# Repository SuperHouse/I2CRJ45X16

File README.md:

I2C to RJ45 Breakout (16 Port)
==============================
Copyright 2019-2021 SuperHouse Automation Pty Ltd  www.superhouse.tv  

24 RJ45 sockets connected to 64 I/O channels via I2C addressable
I/O controllers. Intended for use in building a home automation light
switch controller for connection to SuperHouse light switches.

Features:

 * 16 x RJ45 sockets for connection to light switches over Cat-5
 * I2C interface with interrupt output

This project has different versions:

 * 8-port version: https://github.com/superhouse/i2crj45x8
 * 16-port version: https://github.com/superhouse/i2crj45x16
 * 24-port version: https://github.com/superhouse/i2crj45x24
 * 24-port version with passthrough: https://github.com/superhouse/i2crj45x24pt

More information:

  http://www.superhouse.tv/i2crj45x16

INSTALLATION
------------
The design is saved as an EAGLE project. EAGLE PCB design software is
available from www.cadsoftusa.com free for non-commercial use. To use
this project download it and place the directory containing these files
into the "eagle" directory on your computer. Then open EAGLE and
navigate to the project.

CREDITS
-------
Designed by Jonathan Oxer jon@oxer.com.au

DISTRIBUTION
------------
The specific terms of distribution of this project are governed by the
license referenced below.

LICENSE
-------
Licensed under the TAPR Open Hardware License (www.tapr.org/OHL).
The "license" folder within this repository also contains a copy of
this license in plain text format.

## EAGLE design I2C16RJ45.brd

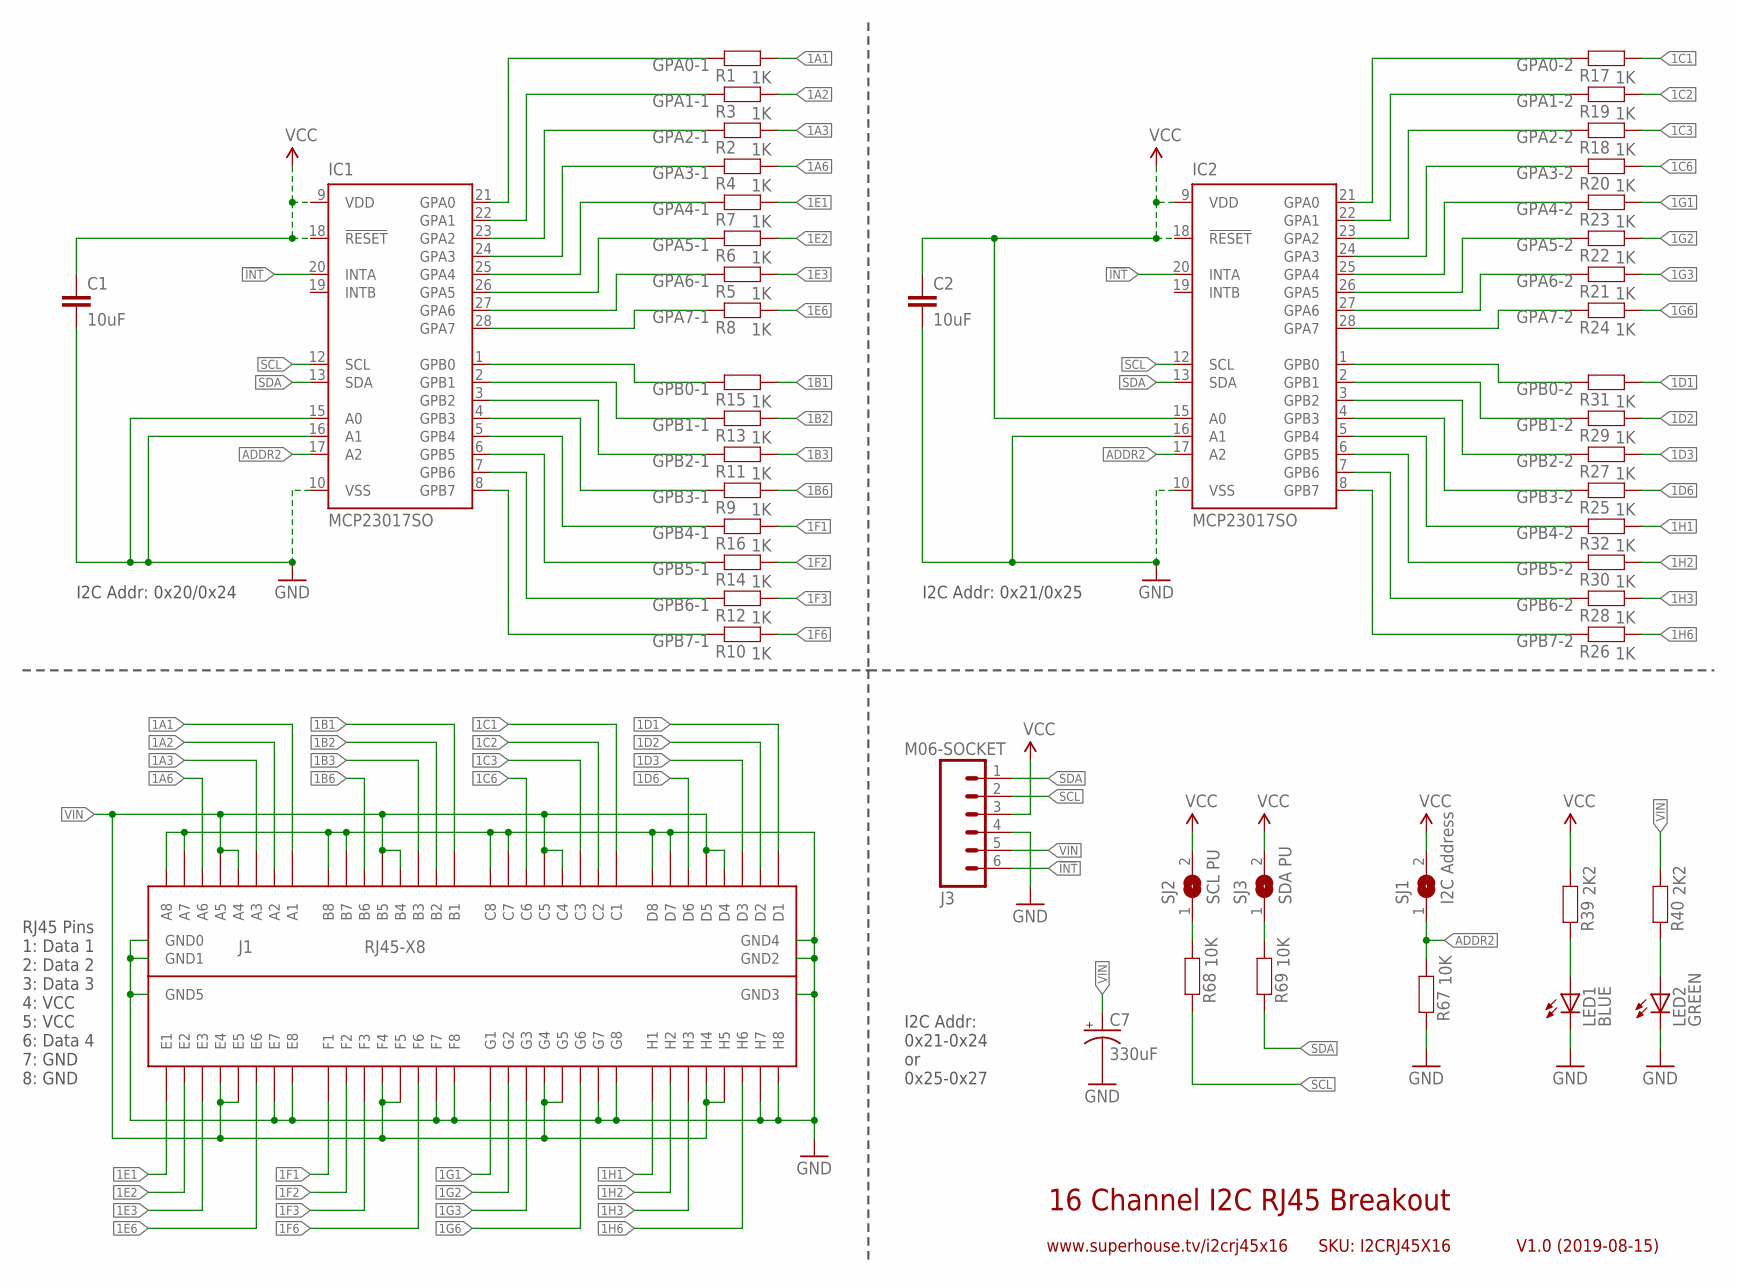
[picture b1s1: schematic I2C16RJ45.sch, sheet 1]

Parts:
C1, C2: 10uF; C0805
C7: 330uF; PANASONIC_G
IC1, IC2: MCP23017SO; SO28W
J1: RJ45-X8; RJ45-2X4
J3: M06-SOCKET; 1X06-S
LED1: BLUE; LED-0603
LED2: GREEN; LED-0603
R1, R2, R3, R4, R5, R6, R7, R8, R9, R10, R11, R12, R13, R14, R15, R16, R17, R18, R19, R20, R21, R22, R23, R24, R25, R26, R27, R28, R29, R30, R31, R32: 1K; R0603
R39, R40: 2K2; R0603
R67, R68, R69: 10K; R0603
SJ1: I2C Address; SJ
SJ2: SCL PU; SJ
SJ3: SDA PU; SJ

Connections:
1A1: J1.A1, R1.2
1A2: J1.A2, R3.2
1A3: J1.A3, R2.2
1A6: J1.A6, R4.2
1B1: J1.B1, R15.2
1B2: J1.B2, R13.2
1B3: J1.B3, R11.2
1B6: J1.B6, R9.2
1C1: J1.C1, R17.2
1C2: J1.C2, R19.2
1C3: J1.C3, R18.2
1C6: J1.C6, R20.2
1D1: J1.D1, R31.2
1D2: J1.D2, R29.2
1D3: J1.D3, R27.2
1D6: J1.D6, R25.2
1E1: J1.E1, R7.2
1E2: J1.E2, R6.2
1E3: J1.E3, R5.2
1E6: J1.E6, R8.2
1F1: J1.F1, R16.2
1F2: J1.F2, R14.2
1F3: J1.F3, R12.2
1F6: J1.F6, R10.2
1G1: J1.G1, R23.2
1G2: J1.G2, R22.2
1G3: J1.G3, R21.2
1G6: J1.G6, R24.2
1H1: J1.H1, R32.2
1H2: J1.H2, R30.2
1H3: J1.H3, R28.2
1H6: J1.H6, R26.2
!INT: IC1.20 (INTA), IC2.20 (INTA), J3.6; also elsewhere on the board
ADDR2: IC1.17 (A2), IC2.17 (A2), R67.2, SJ1.1; also elsewhere on the board
GND: C1.2, C2.2, C7.-, IC1.10 (VSS), IC1.15 (A0), IC1.16 (A1), IC2.10 (VSS), IC2.16 (A1), J1.A7, J1.A8, J1.B7, J1.B8, J1.C7, J1.C8, J1.D7, J1.D8, J1.E7, J1.E8, J1.F7, J1.F8, J1.G7, J1.G8, J1.GND0, J1.GND1, J1.GND2, J1.GND3, J1.GND4, J1.GND5, J1.H7, J1.H8, J3.4, LED1.C, LED2.C, R67.1; also elsewhere on the board
GPA0-1: IC1.21 (GPA0), R1.1
GPA0-2: IC2.21 (GPA0), R17.1
GPA1-1: IC1.22 (GPA1), R3.1
GPA1-2: IC2.22 (GPA1), R19.1
GPA2-1: IC1.23 (GPA2), R2.1
GPA2-2: IC2.23 (GPA2), R18.1
GPA3-1: IC1.24 (GPA3), R4.1
GPA3-2: IC2.24 (GPA3), R20.1
GPA4-1: IC1.25 (GPA4), R7.1
GPA4-2: IC2.25 (GPA4), R23.1
GPA5-1: IC1.26 (GPA5), R6.1
GPA5-2: IC2.26 (GPA5), R22.1
GPA6-1: IC1.27 (GPA6), R5.1
GPA6-2: IC2.27 (GPA6), R21.1
GPA7-1: IC1.28 (GPA7), R8.1
GPA7-2: IC2.28 (GPA7), R24.1
GPB0-1: IC1.1 (GPB0), R15.1
GPB0-2: IC2.1 (GPB0), R31.1
GPB1-1: IC1.2 (GPB1), R13.1
GPB1-2: IC2.2 (GPB1), R29.1
GPB2-1: IC1.3 (GPB2), R11.1
GPB2-2: IC2.3 (GPB2), R27.1
GPB3-1: IC1.4 (GPB3), R9.1
GPB3-2: IC2.4 (GPB3), R25.1
GPB4-1: IC1.5 (GPB4), R16.1
GPB4-2: IC2.5 (GPB4), R32.1
GPB5-1: IC1.6 (GPB5), R14.1
GPB5-2: IC2.6 (GPB5), R30.1
GPB6-1: IC1.7 (GPB6), R12.1
GPB6-2: IC2.7 (GPB6), R28.1
GPB7-1: IC1.8 (GPB7), R10.1
GPB7-2: IC2.8 (GPB7), R26.1
unnamed: R68.2, SJ2.1
unnamed: R69.2, SJ3.1
unnamed: LED1.A, R39.1
unnamed: LED2.A, R40.1
SCL: IC1.12 (SCL), IC2.12 (SCL), J3.2, R68.1; also elsewhere on the board
SDA: IC1.13 (SDA), IC2.13 (SDA), J3.1, R69.1; also elsewhere on the board
VCC: C1.1, C2.1, IC1.9 (VDD), IC1.18 (!RESET), IC2.9 (VDD), IC2.15 (A0), IC2.18 (!RESET), J3.3, R39.2, SJ1.2, SJ2.2, SJ3.2; also elsewhere on the board
VIN: C7.+, J1.A4, J1.A5, J1.B4, J1.B5, J1.C4, J1.C5, J1.D4, J1.D5, J1.E4, J1.E5, J1.F4, J1.F5, J1.G4, J1.G5, J1.H4, J1.H5, J3.5, R40.2; also elsewhere on the board

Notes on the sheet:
RJ45 Pins 1: Data 1 2: Data 2 3: Data 3 4: VCC 5: VCC 6: Data 4 7: GND 8: GND
16 Channel I2C RJ45 Breakout
V1.0 (2019-08-15)
www.superhouse.tv/i2crj45x16
SKU: I2CRJ45X16
I2C Addr: 0x20/0x24
I2C Addr: 0x21/0x25
I2C Addr: 0x21-0x24 or 0x25-0x27

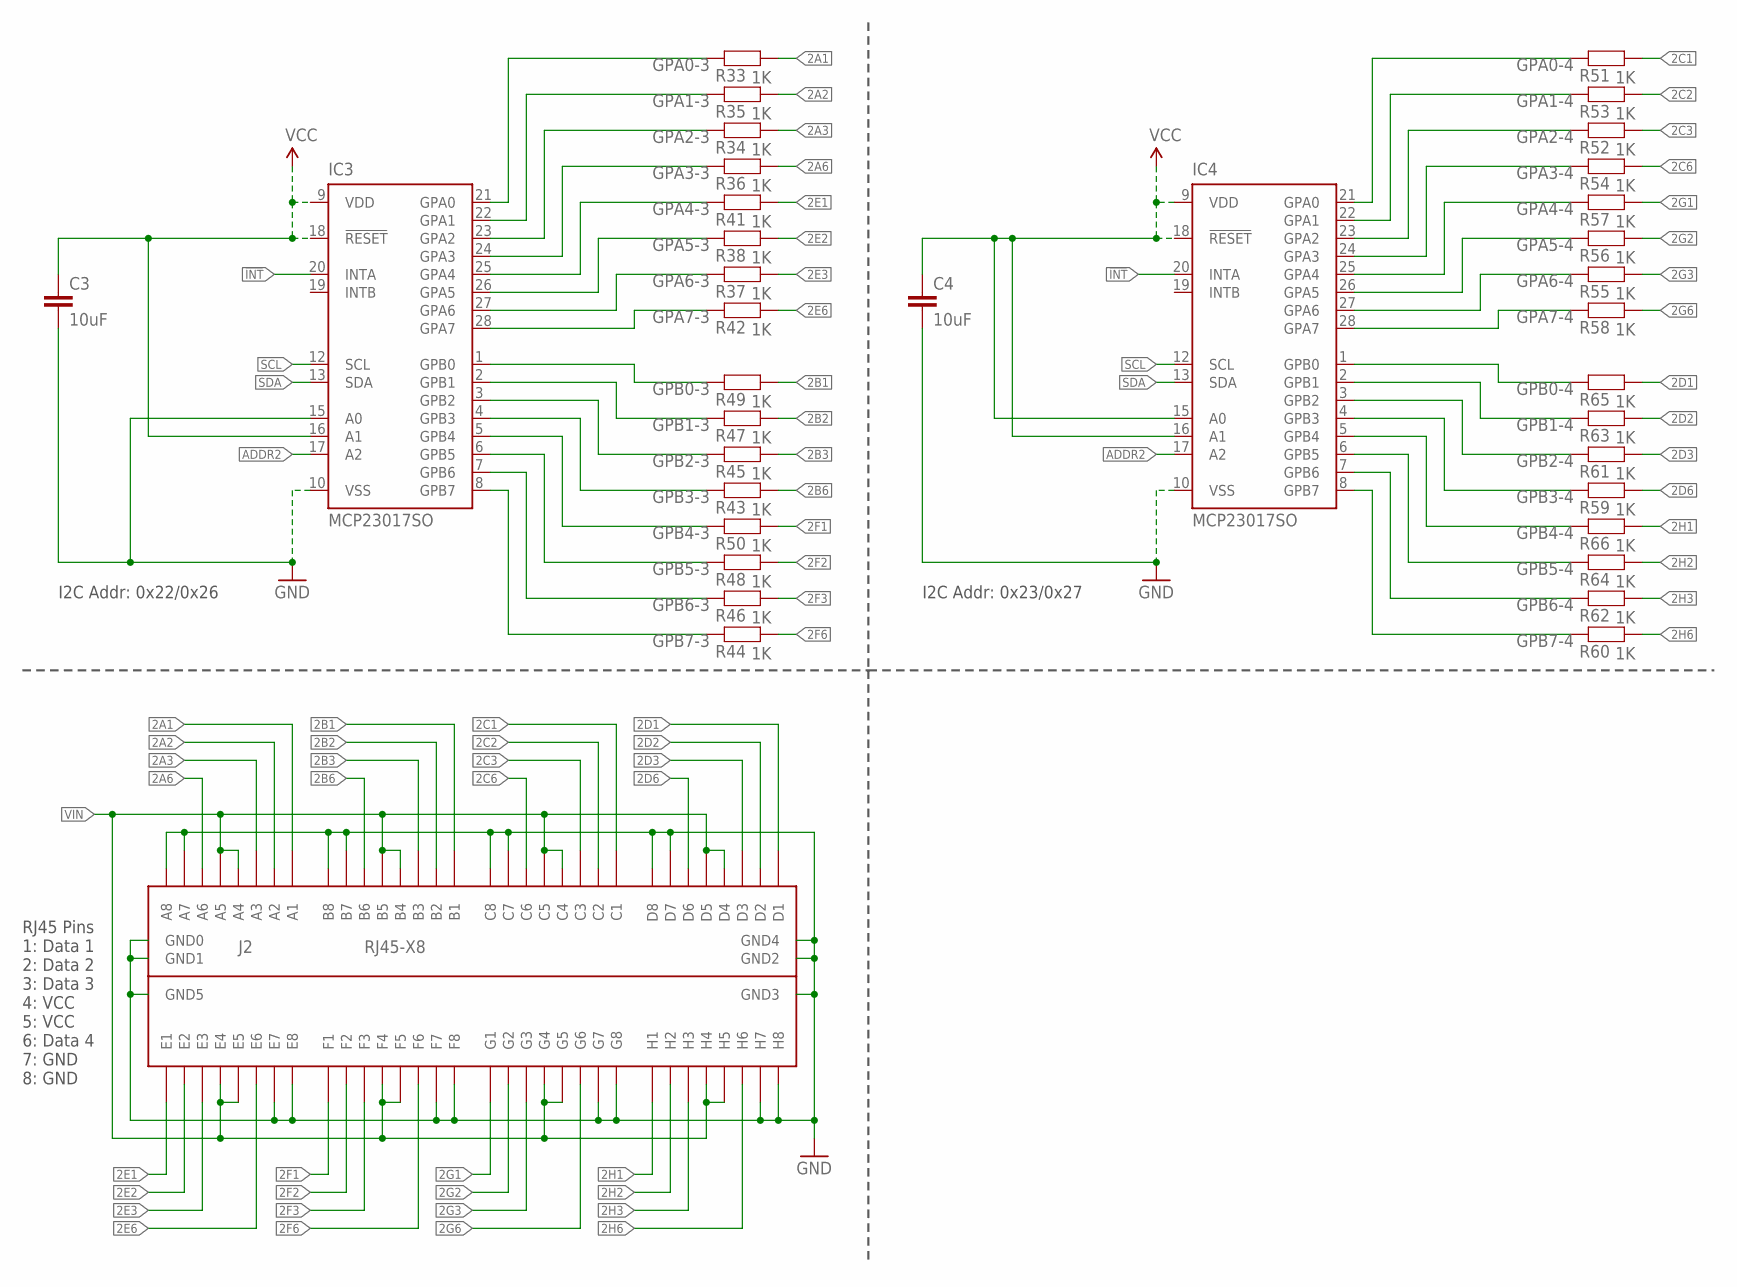
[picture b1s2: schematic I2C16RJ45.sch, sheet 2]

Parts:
C3, C4: 10uF; C0805
IC3, IC4: MCP23017SO; SO28W
J2: RJ45-X8; RJ45-2X4
R33, R34, R35, R36, R37, R38, R41, R42, R43, R44, R45, R46, R47, R48, R49, R50, R51, R52, R53, R54, R55, R56, R57, R58, R59, R60, R61, R62, R63, R64, R65, R66: 1K; R0603

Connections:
2A1: J2.A1, R33.2
2A2: J2.A2, R35.2
2A3: J2.A3, R34.2
2A6: J2.A6, R36.2
2B1: J2.B1, R49.2
2B2: J2.B2, R47.2
2B3: J2.B3, R45.2
2B6: J2.B6, R43.2
2C1: J2.C1, R51.2
2C2: J2.C2, R53.2
2C3: J2.C3, R52.2
2C6: J2.C6, R54.2
2D1: J2.D1, R65.2
2D2: J2.D2, R63.2
2D3: J2.D3, R61.2
2D6: J2.D6, R59.2
2E1: J2.E1, R41.2
2E2: J2.E2, R38.2
2E3: J2.E3, R37.2
2E6: J2.E6, R42.2
2F1: J2.F1, R50.2
2F2: J2.F2, R48.2
2F3: J2.F3, R46.2
2F6: J2.F6, R44.2
2G1: J2.G1, R57.2
2G2: J2.G2, R56.2
2G3: J2.G3, R55.2
2G6: J2.G6, R58.2
2H1: J2.H1, R66.2
2H2: J2.H2, R64.2
2H3: J2.H3, R62.2
2H6: J2.H6, R60.2
!INT: IC3.20 (INTA), IC4.20 (INTA); also elsewhere on the board
ADDR2: IC3.17 (A2), IC4.17 (A2); also elsewhere on the board
GND: C3.2, C4.2, IC3.10 (VSS), IC3.15 (A0), IC4.10 (VSS), J2.A7, J2.A8, J2.B7, J2.B8, J2.C7, J2.C8, J2.D7, J2.D8, J2.E7, J2.E8, J2.F7, J2.F8, J2.G7, J2.G8, J2.GND0, J2.GND1, J2.GND2, J2.GND3, J2.GND4, J2.GND5, J2.H7, J2.H8; also elsewhere on the board
GPA0-3: IC3.21 (GPA0), R33.1
GPA0-4: IC4.21 (GPA0), R51.1
GPA1-3: IC3.22 (GPA1), R35.1
GPA1-4: IC4.22 (GPA1), R53.1
GPA2-3: IC3.23 (GPA2), R34.1
GPA2-4: IC4.23 (GPA2), R52.1
GPA3-3: IC3.24 (GPA3), R36.1
GPA3-4: IC4.24 (GPA3), R54.1
GPA4-3: IC3.25 (GPA4), R41.1
GPA4-4: IC4.25 (GPA4), R57.1
GPA5-3: IC3.26 (GPA5), R38.1
GPA5-4: IC4.26 (GPA5), R56.1
GPA6-3: IC3.27 (GPA6), R37.1
GPA6-4: IC4.27 (GPA6), R55.1
GPA7-3: IC3.28 (GPA7), R42.1
GPA7-4: IC4.28 (GPA7), R58.1
GPB0-3: IC3.1 (GPB0), R49.1
GPB0-4: IC4.1 (GPB0), R65.1
GPB1-3: IC3.2 (GPB1), R47.1
GPB1-4: IC4.2 (GPB1), R63.1
GPB2-3: IC3.3 (GPB2), R45.1
GPB2-4: IC4.3 (GPB2), R61.1
GPB3-3: IC3.4 (GPB3), R43.1
GPB3-4: IC4.4 (GPB3), R59.1
GPB4-3: IC3.5 (GPB4), R50.1
GPB4-4: IC4.5 (GPB4), R66.1
GPB5-3: IC3.6 (GPB5), R48.1
GPB5-4: IC4.6 (GPB5), R64.1
GPB6-3: IC3.7 (GPB6), R46.1
GPB6-4: IC4.7 (GPB6), R62.1
GPB7-3: IC3.8 (GPB7), R44.1
GPB7-4: IC4.8 (GPB7), R60.1
SCL: IC3.12 (SCL), IC4.12 (SCL); also elsewhere on the board
SDA: IC3.13 (SDA), IC4.13 (SDA); also elsewhere on the board
VCC: C3.1, C4.1, IC3.9 (VDD), IC3.16 (A1), IC3.18 (!RESET), IC4.9 (VDD), IC4.15 (A0), IC4.16 (A1), IC4.18 (!RESET); also elsewhere on the board
VIN: J2.A4, J2.A5, J2.B4, J2.B5, J2.C4, J2.C5, J2.D4, J2.D5, J2.E4, J2.E5, J2.F4, J2.F5, J2.G4, J2.G5, J2.H4, J2.H5; also elsewhere on the board

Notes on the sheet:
RJ45 Pins 1: Data 1 2: Data 2 3: Data 3 4: VCC 5: VCC 6: Data 4 7: GND 8: GND
I2C Addr: 0x22/0x26
I2C Addr: 0x23/0x27

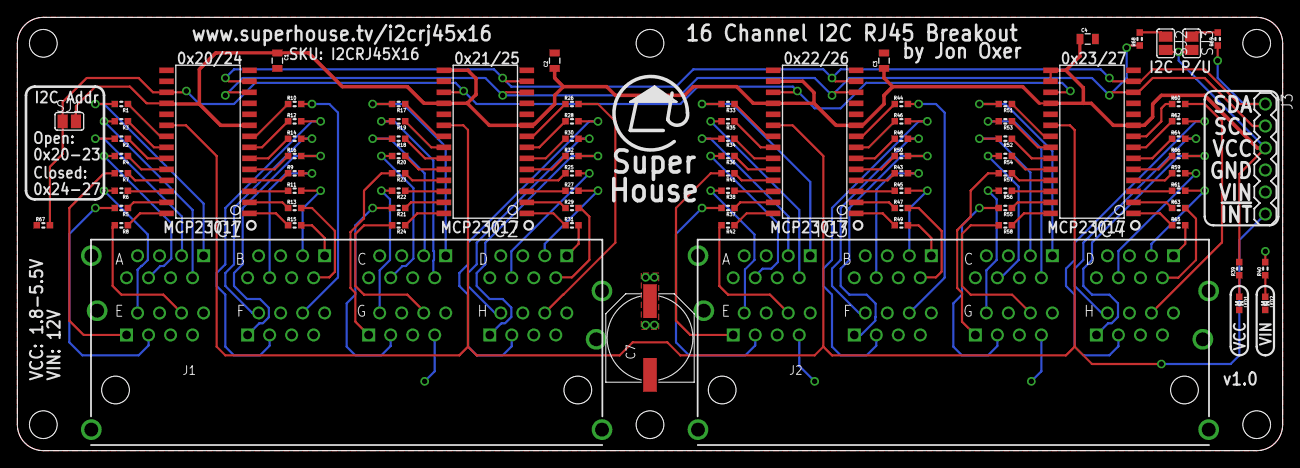
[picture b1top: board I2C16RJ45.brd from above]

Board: 2 copper layers, 146.0 x 50.0 mm, 86 parts (0 on the bottom side), 139 nets.

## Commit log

2019-08-15 Routing
2019-08-15 Renamed files for v1.0 release
2019-09-07 Board and schematic labelling
2019-09-07 Added fiducials
2021-04-12 Moved hardware files into subdirectory.
2021-04-15 Renamed existing project files.
2021-04-15 Replaced project files with major redesign for v3.0 release.
2021-04-15 Major rework based on 24-port version.
2021-04-15 Added v3.0 render.
2021-04-15 Added render and links to other versions to README.
2021-04-15 Added .gitignore.
2021-04-15 Added link to 24-port version with passthrough.

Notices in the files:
I2C16RJ45.brd:
Copyright 2019 SuperHouse Automation Pty Ltd
